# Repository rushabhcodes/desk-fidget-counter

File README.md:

# Desk fidget counter

A USB-powered scroll ring with a fixed **1.28-inch round display**. It counts complete turns, retains the count in FRAM, and shows your computer’s clock, CPU/RAM usage and battery through a USB companion app.

Short-press the front button to switch between scrolling and counting only. Hold for three seconds to clear the count. The screen and cable stay fixed while the outer grip rotates.

## Board and enclosure

- **Two-layer, 1.6 mm PCB**, with all 52 fitted components on top. USB-C is on the rear; a 14×7 mm curved button with guided travel and foam return operates the front Omron switch.
- **Six product prints and four screws**, in an approximately **Ø89.4 × 19.5 mm** body, with the button inside its circular outline. The optical skirt is integral to the grip; the screen carrier and bezel share two screws.
- **One complete 6712ZZ bearing object** in the CAD viewer, including its races, shields, balls and cage. Calibrate the printed bearing fits with the coupons before printing the enclosure.
- The source defines connectivity, supplier footprints, placement and fabrication rules. F1 uses independently checked external routing through TSCircuit’s documented custom-router interface; the stored copper is guarded against changes to its input. See [routing](routing/README.md).

**Current electronics: RP2040 PCB F1 / firmware 6.0.0.** The STM32 has been replaced with an RP2040, 2 MB Winbond boot flash, a 12 MHz Abracon crystal, local supply bypassing and 27 Ω USB termination. The PCB outline and connector, sensor and switch datums remain compatible with the Ø89.4 mm E14 enclosure and its recessed circular button. Local circuit, fabrication and assembly checks pass for a first prototype. The older E6 archive targets STM32; use the matching [F1 fabrication kit](release/desk-knob-f1-e14-fabrication.zip). See [readiness](validation/readiness.json) and the [firmware/programming guide](firmware/README.md).

[Visual CAD audit](mechanical/AUDIT.md): fourteen inspection views, corrected carrier screw bores and reserved space for screen rear electronics; enclosure height remains 19.5 mm.

[E14 visual review](mechanical/VISUAL-REVIEW.md): a continuous fixed collar covers the open underside of the screen bezel. It belongs to the existing carrier and retains the 0.8 mm rotating seam, body dimensions, six prints and four screws.

Widget v6.0.4 includes the upstream copper-pour visibility fix. Both the C1 pad connection and its long GND continuation are visible. [Trace visibility checks](validation/TRACE-VISIBILITY.md)

## What to buy outside JLCPCB

Quantities below are for **one complete device**. A complete JLCPCB **assembly** order supplies the PCB and its 52 fitted electronic components, including the MCU, optical sensor, FRAM, USB connector, front button, J4 programming header and J6 removable display header. A bare-PCB order supplies the board only.

| Qty | Buy or supply separately | Specification and purpose |
|---|---|---|
| 1 kit | [Waveshare 19192 display](https://www.waveshare.com/product/1.28inch-lcd-module.htm) | Non-touch, 1.28-inch, 240×240 GC9A01 module. The supplied PH-to-jumper lead is unused. Connect using replacement H1 below. |
| 1 | [Complete 6712ZZ bearing](https://maysmeprecision.com/Show/?Cid=677) | **60 mm bore × 75 mm OD × 7 mm**, double metal shields. Buy the assembled bearing; its internal balls/races are not separate purchases. |
| 6 | [E14 printed enclosure parts](mechanical/stl) | `base`, `lid`, `knob`, `screen-carrier`, `screen-bezel`, `button-cap`. PLA; the grip’s integral optical track must be **opaque at 950 nm**. Black colour alone does not establish this. Print the fit coupons first. |
| 2 | Countersunk **DIN 965 M2×6** screws | Attach the base and lid. Nominal head Ø3.8 mm; check the actual purchased head/drive against the model. |
| 2 | Countersunk **DIN 965 M2×10** screws | One shared pair retains the screen bezel and carrier on the braced screw supports. |
| 1 small piece | [PORON 4701-30-20062-04 foam](https://www.rogerscorp.com/elastomeric-material-solutions/poron-industrial-polyurethanes/poron-4701-30) | **1.57 mm** nominal, 320 kg/m³. Cut four Ø4 mm and two Ø2.6 mm PCB capture pads, plus four 2×1.6 mm pieces for two stacked button-return pads; a 20×20 mm sample is sufficient. |
| 1 small piece | [3M 467MP transfer adhesive](https://www.3m.com/3M/en_US/p/dc/v000185218/) | **0.05 mm** adhesive for the six PCB pads and the two stacked button-return pads. The integral optical skirt needs no separate adhesive joint. |
| As needed | [3M 5413 polyimide tape](https://www.3m.co.uk/3M/en_GB/p/d/v000091659/) | **0.069 mm** insulation over inspected underside solder wells. Trim through-hole tails/joints to the documented ≤0.8 mm allowance first. |
| 1 assembled lead | **H1 keyed display harness** | Order a crimped **JST SHR-08V-S-B to PHR-8**, eight wires, straight circuit mapping 1→1 through 8→8, **44±1 mm free insulation between rear housing exits**. [Parts and drawing](manufacturing/WIRING.md). This custom lead is separate from both the display kit and JLCPCB assembly. |
| 1, reuse if suitable | USB data cable | USB-C at the device; ordinary USB 2.0 data is sufficient. Check the plug against the enclosure’s documented 13.4×6.9 mm approach gauge. |
| Optional: 3 | Adhesive silicone feet | Approximately Ø5×1 mm. These add 1 mm to the nominal body height. |

**H1 is a replacement crimped cable, purchased separately. J6’s keyed JST-SH socket is fitted by JLCPCB, including in the SMT-only option.** The display, bearing, printed parts and final wiring/mechanical assembly are not supplied as part of PCB assembly.

### Programming equipment and tools

These items are reusable and removed before closing the enclosure:

| Qty | Item | Requirement |
|---|---|---|
| 1 | SWD programmer | CMSIS-DAP / Raspberry Pi Debug Probe supporting RP2040. USB powers the board; VTref is a sense connection. |
| 1 | J4 programming lead | JST **PHR-6**, 2.0 mm PH series, with the correct probe-end termination. A precrimped lead can be used. If making it, use six **SPH-004T-P0.5S** contacts plus spares and qualified 32–28 AWG wire, insulation Ø0.5–0.9 mm. See the [physical pin map](https://github.com/rushabhcodes/desk-fidget-counter/blob/main/manufacturing/WIRING.md). |
| 1, only for SMT-only PCBA | J4 board header | The **51-placement SMT-only** option includes J6 and leaves only **JST B6B-PH-K-S(LF)(SN), C131342** for local through-hole soldering. Complete assembly has 52 placements. |

Have solder/flux and a soldering setup, wire stripper, flush cutters, multimeter, caliper, an M2×0.4 tap and a screwdriver matching your screws. Follow the [printing and fit guide](mechanical/FIT.md); the supplied print orientations and support notes matter.

## Software and controls

Flash firmware 6.0.0 through J4 SWD or the RP2040 USB UF2 bootloader, then initialize a fresh FRAM with a three-second button hold or the explicit console command in the [firmware guide](https://github.com/rushabhcodes/desk-fidget-counter/blob/main/firmware/README.md).

For laptop information:

```sh
python -m pip install -r companion/requirements.txt
python companion/dashboard.py
```

The [companion guide](https://github.com/rushabhcodes/desk-fidget-counter/blob/main/companion/README.md) covers macOS, Windows and Linux. Counting and scrolling work without the companion while USB is awake. USB suspend switches the display and encoder off; turns during suspend are not measured.

## Build and validation

```sh
bun install --frozen-lockfile
bun run typecheck && bun run test:route-display && bun run test
bun run check:netlist && bun run check:schematic
bun run build
bun run check:placement && bun validation/check-design.mjs
bun run check:footprints && bun run check:shorts && bun run check:assembly
```

The lockfile pins tscircuit `0.0.3157`, core `0.0.2340` and the CLI’s KiCad export dependency. Regenerate the PCB, schematic and 3D snapshots with `bun run tsci snapshot '*.circuit.tsx' --update --3d`.

`assembly.circuit.tsx` is the complete product; `index.circuit.tsx` is the bare PCB. The build stages the checked full assembly at `dist/circuit.json` for publication. Source, package CAD, prints and wiring are included in the repository. The [F1/E14 fabrication kit](release/desk-knob-f1-e14-fabrication.zip) includes matching Gerbers, BOM/CPL, physical pin maps, independent checks and RP2040 firmware. Follow the [upload guide](manufacturing/current/README.md). Final factory preview and physical prototype bring-up remain; no supplier upload or order has been made.

- [Assembly steps](https://github.com/rushabhcodes/desk-fidget-counter/blob/main/ASSEMBLY.md) · [Wiring and programming connections](https://github.com/rushabhcodes/desk-fidget-counter/blob/main/manufacturing/WIRING.md)
- [Mechanical source and CAD](https://github.com/rushabhcodes/desk-fidget-counter/blob/main/mechanical/README.md) · [Model provenance and limitations](https://github.com/rushabhcodes/desk-fidget-counter/blob/main/mechanical/vendor/README.md)
- [Manufacturing requirements](https://github.com/rushabhcodes/desk-fidget-counter/blob/main/manufacturing/README.md) · [Validation results](https://github.com/rushabhcodes/desk-fidget-counter/blob/main/validation/REPORT.md) · [First-prototype bring-up](https://github.com/rushabhcodes/desk-fidget-counter/blob/main/validation/BRINGUP.md)

Inspired by the [Ploopy Knob](https://ploopy.co/knob/) and [original fidget counter](https://tscircuit.com/rushabhcodes/fidget-counter). Project code and original geometry are MIT; purchased-part assets retain their upstream rights.

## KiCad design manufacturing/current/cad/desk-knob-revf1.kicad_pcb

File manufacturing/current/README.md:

# Desk knob — RP2040 PCB F1 / enclosure E14

Checked 10 November 2026 against the current source. Local circuit, independent fabrication and assembly checks pass for **first-prototype manufacture**. This kit contains RP2040 hardware and firmware 6.0.0, with the recessed curved button inside the Ø89.4×19.5 mm E14 enclosure. Final manufacturer DFM/feeder preview and physical bring-up remain. No supplier upload, purchase or stock allocation was performed.

## Upload files

1. Upload **Gerbers-F1.zip** for PCB fabrication. The outer review ZIP also contains CAD, evidence, firmware and prints; it is not the Gerber upload.
2. For **52-part complete assembly**, upload **BOM-complete.csv + CPL-complete.csv** and confirm a service including the J4 through-hole header.
3. For **51-part SMT assembly**, upload **BOM-smt.csv + CPL-smt.csv**. Fit only J4, JST B6B-PH-K-S(LF)(SN) / C131342, locally. J6 is already fitted.
4. Check every exact MPN, feeder origin, asymmetric rotation and pin 1 against **physical-pin-map.csv** and **assembly/assembly-top.svg** before payment. CPL and Gerbers share their origin, including negative Y; do not mirror, take absolute coordinates or edit rotations independently.

## Board settings

| Item | Specification |
|---|---|
| Material | FR-4, Tg ≥135°C |
| Layers / copper / thickness | 2 layers / 1 oz / 1.6 mm nominal |
| Finish / mask / silk | ENIG / green / white |
| Unit outline | 68×83.5 mm clipped round profile with USB/button tabs |
| Internal window | 34.6×40.6 mm, R2 corners; preserve the Gerber contour |
| Vias | 50 at Ø0.20 drill / Ø0.50 pad; 48 at Ø0.30 / Ø0.60 mm |
| Copper rules | ≥0.10 mm track/gap, ≥0.15 mm component-pad gap, ≥0.30 mm edge clearance |
| USB shield slots | Four plated 0.60×1.50/1.60 mm slots |
| Assembly | 52 top placements / 27 exact MPN BOM lines |

E14 adds a continuous fixed collar to the existing screen carrier. Keep the 0.8 mm rotating seam open; see enclosure/VISUAL-REVIEW.md for the complete visual review. The body remains Ø89.4×19.5 mm with six prints and four screws.

The 98 vias retain ≥0.15 mm annular rings and their drills do not intersect SMT paste. No via-in-pad process is required. Confirm tooling/support for the irregular outline and large internal window; removable panel rails must stay outside the finished outline. USB full-speed signal integrity has not been measured.

## Product assembly and programming

J4 is the only through-hole header. Trim its underside tails/joints to ≤0.8 mm, inspect/deburr and insulate the specified solder wells before enclosure assembly. The Waveshare display, complete 6712ZZ bearing, six printed parts, screws, foam and custom H1 harness are separate from PCBA. H1 is a keyed crimped SH8-to-PH8 lead, 44±1 mm free insulation, straight circuits 1→1 through 8→8; see **WIRING.md** and **LCD-harness.csv**. The display kit's jumper lead is unused.

**enclosure/stl/** contains the six E14 product prints and three fit coupons. Follow the print poses and fit notes, and use **ASSEMBLY.md** for the sequence. Actual printed fits, optical opacity and button force/life require validation.

Use **firmware/desk-knob.uf2** with the RP2040 ROM USB bootloader or **firmware/desk-knob.elf** through J4 SWD. See **firmware/README.md** for the exact procedure. Initialize a fresh FRAM deliberately with a three-second button hold, then perform **BRINGUP.md** checks. Historical STM32 programming procedures and images do not apply.

## Evidence and file integrity

**checks/** includes zero-violation/zero-open KiCad DRC, native-copper/pad/drill preservation, Gerber/Excellon parsing, BOM/CPL and physical pin maps, annuli/paste clearances, local signal paths, firmware image and assembly audit evidence. All 27 exact part identities were publicly purchasable on 10 November 2026; stock is unreserved. Final allocation, purchasing/attrition quantities and feeder/rotation approval require the factory quote/preview. MCU unit pricing does not establish a lower complete PCBA price.

**cad/** contains the finalized source-derived KiCad board/project/rules and exact generated footprints. **manifest.json** binds the kit to the checked source. **SHA256SUMS.txt** covers every kit file except itself. Keep this F1 hardware, BOM/CPL and firmware together.

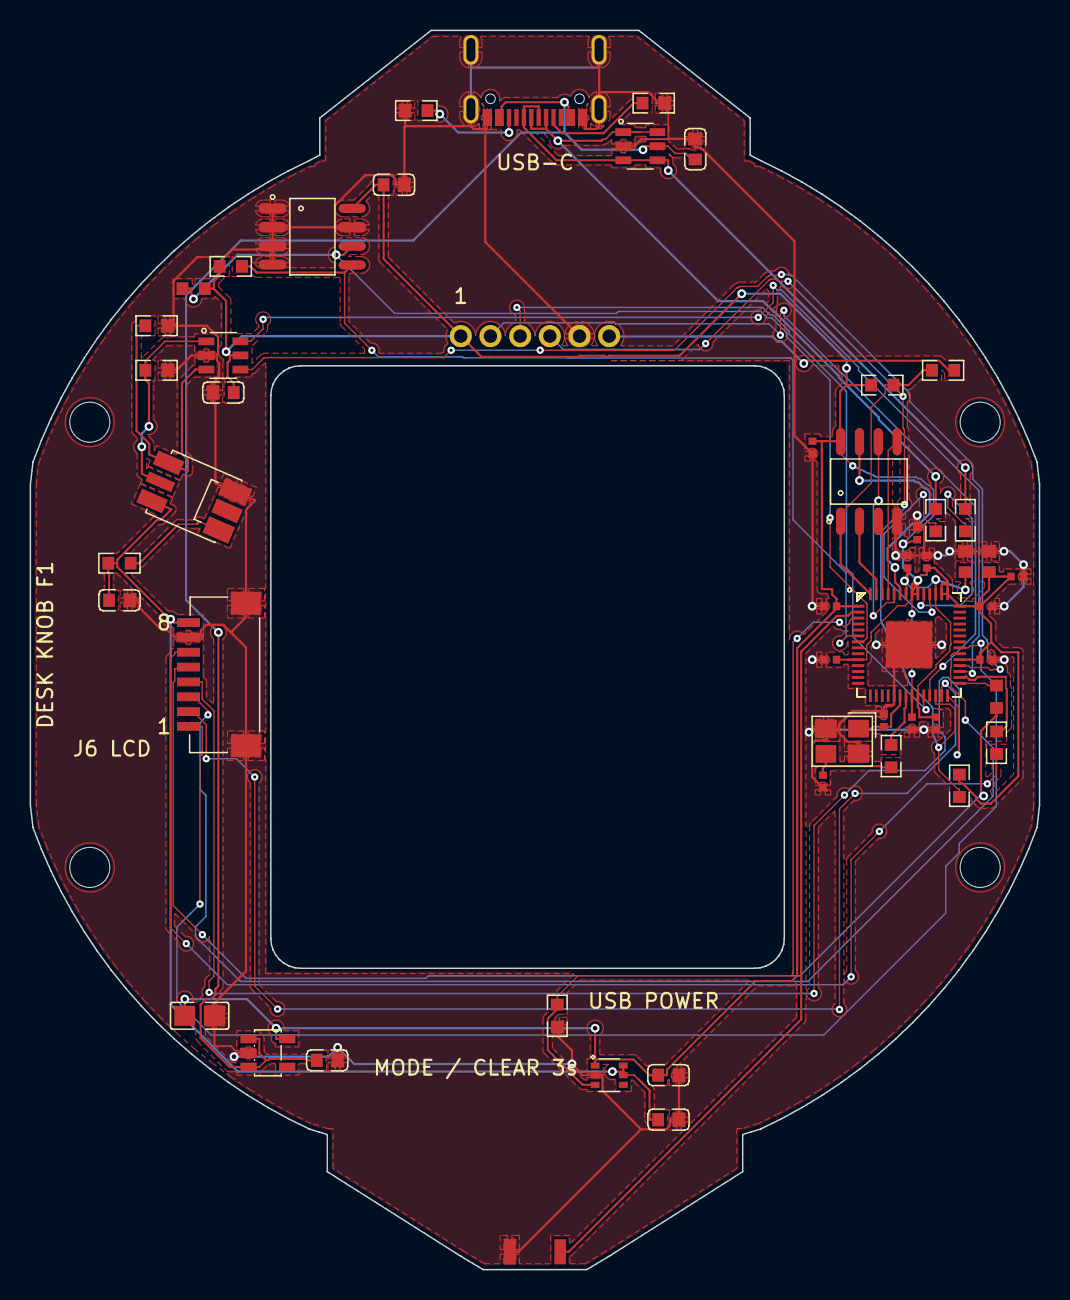
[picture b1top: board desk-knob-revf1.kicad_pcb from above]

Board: 2 copper layers, 68.0 x 83.5 mm, 52 parts (0 on the bottom side), 41 nets.

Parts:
C1: 100nF; GRM188R71C104KA01D__C1
C2: 1uF; GRM188R61A105KA61D__C2
C3: 1uF; GRM188R61A105KA61D__C3
C5: 1uF; GRM188R61A105KA61D__C5
C6: 4.7uF; CL21A475KOFNNNE__C6
C7: 100nF; GRM155R71C104KA88D__C7
C8: 100nF; GRM155R71C104KA88D__C8
C9: 100nF; GRM155R71C104KA88D__C9
C10: 100nF; GRM155R71C104KA88D__C10
C11: 100nF; GRM155R71C104KA88D__C11
C12: 100nF; GRM155R71C104KA88D__C12
C13: 100nF; GRM155R71C104KA88D__C13
C14: 100nF; GRM188R71C104KA01D__C14
C15: 1uF; GRM188R61A105KA61D__C15
C16: 100nF; GRM188R71C104KA01D__C16
C17: 100nF; GRM155R71C104KA88D__C17
C18: 100nF; GRM155R71C104KA88D__C18
C19: 100nF; GRM155R71C104KA88D__C19
C20: 1uF; GRM188R61A105KA61D__C20
C21: 1uF; GRM188R61A105KA61D__C21
C22: 100nF; GRM155R71C104KA88D__C22
C23: 15pF; 0402CG150J500NT__C23
C24: 15pF; 0402CG150J500NT__C24
J1: J1; TYPEC-309-ACP16L65__J1
J4: J4; B6B-PH-K-S_LF_SN__J4
J6: J6; SM08B-SRSS-TB_LF_SN__J6
R1: 5.1kΩ; RC0603FR-075K1L__R1
R2: 5.1kΩ; RC0603FR-075K1L__R2
R3: 27Ω; 0603WAF270JT5E__R3
R4: 27Ω; 0603WAF270JT5E__R4
R5: 1kΩ; 0603WAF1001T5E__R5
R6: 1kΩ; 0603WAF1001T5E__R6
R7: 10kΩ; RC0603FR-0710KL__R7
R10: 10kΩ; RC0603FR-0710KL__R10
R12: 4.7kΩ; RC0603FR-074K7L__R12
R13: 4.7kΩ; RC0603FR-074K7L__R13
R21: 100kΩ; RC0603FR-07100KL__R21
R24: 150Ω; RC0603FR-07150RL__R24
R25: 22kΩ; RC0603FR-0722KL__R25
R26: 22kΩ; RC0603FR-0722KL__R26
R27: 22Ω; RC0603FR-0722RL__R27
R28: 22Ω; RC0603FR-0722RL__R28
SW1: SW1; B3U-3000P__SW1
U1: RP2040; RP2040__U1
U2: TCUT1600X01; TCUT1600X01__U2
U3: MB85RC256VPNF-G-AMERE2; MB85RC256VPNF-G-AMERE2__U3
U4: TPS22919DCKR; TPS22919DCKR__U4
U5: TLV75533PDBVR; TLV75533PDBVR__U5
U6: USBLC6-2SC6; USBLC6-2SC6__U6
U7: SN74LVC2G17DBVR; SN74LVC2G17DBVR__U7
U8: W25Q16JVSNIQ; W25Q16JVSNIQ__U8
X1: X1; ABM8-272-T3__X1

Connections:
BOOTSEL: J4.6, R6.2
CC1: J1.39, R1.1
CC2: J1.33, R2.1
ENC_A: U1.31, U7.6
ENC_B: U1.32, U7.4
GND: C1.2, C2.2, C3.2, C5.2, C6.2, C7.2, C8.2, C9.2, C10.2, C11.2, C12.2, C13.2, C14.2, C15.2, C16.2, C17.2, C18.2, C19.2, C20.2, C21.2, C22.2, C23.2, C24.2, J1.25, J1.26, J1.27, J1.28, J1.29, J1.30, J1.43, J1.44, J4.5, J6.7, J6.9, J6.10, R1.2, R2.2, R21.2, R25.2, R26.2, SW1.2, U1.19, U1.57, U2.3, U3.1, U3.2, U3.3, U3.4, U3.7, U4.2, U5.2, U6.2, U7.2, U8.4, X1.2, X1.4
IR_A: R24.2, U2.1
LCD_BL: J6.1, U1.35
LCD_CS: J6.4, U1.28
LCD_DC: J6.3, U1.34
LCD_MOSI: J6.6, R28.2
LCD_RST: J6.2, U1.27
LCD_SCK: J6.5, R27.2
MODE_BTN: SW1.1, U1.2
OPT_A: R25.1, U2.5, U7.1
OPT_B: R26.1, U2.4, U7.3
PERIPH_3V3: C3.1, C15.1, J6.8, R24.1, U2.6, U4.5, U4.6
PERIPH_EN: R21.1, U1.3, U4.3
QSPI_SCLK: U1.52, U8.6
QSPI_SD0: U1.53, U8.5
QSPI_SD1: U1.55, U8.2
QSPI_SD2: U1.54, U8.3
QSPI_SD3: U1.51, U8.7
QSPI_SS: R6.1, R7.1, U1.56, U8.1
RUN: J4.4, R10.1, U1.26
SCL: R13.2, U1.7, U3.6
SDA: R12.2, U1.6, U3.5
SPI_MOSI: R28.1, U1.30
SPI_SCK: R27.1, U1.29
SWCLK: J4.3, U1.24
SWDIO: J4.2, U1.25
USB_DM: J1.36, J1.38, R3.2, U6.1, U6.6
USB_DM_MCU: R3.1, U1.46
USB_DP: J1.35, J1.37, R4.2, U6.3, U6.4
USB_DP_MCU: R4.1, U1.47
V1V1: C18.1, C19.1, C21.1, U1.23, U1.45, U1.50
V3V3: C2.1, C6.1, C7.1, C8.1, C9.1, C10.1, C11.1, C12.1, C13.1, C14.1, C16.1, C17.1, C20.1, C22.1, J4.1, R7.2, R10.2, R12.1, R13.1, U1.1, U1.10, U1.22, U1.33, U1.42, U1.43, U1.44, U1.48, U1.49, U3.8, U4.1, U5.5, U7.5, U8.8
VBUS: C1.1, C5.1, J1.31, J1.32, J1.41, J1.42, U5.1, U5.3, U6.5
XIN: C23.1, U1.20, X1.1
XOUT: R5.1, U1.21
XTAL_OUT: C24.1, R5.2, X1.3

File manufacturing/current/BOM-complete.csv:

Comment,Designator,Footprint,LCSC Part #,Manufacturer,MPN
GRM188R71C104KA01D / 100nF 16V X7R 10%,"C1,C14,C16",0603,C45000,Murata Electronics,GRM188R71C104KA01D
GRM188R61A105KA61D / 1uF 10V X5R 10%,"C2,C3,C5,C15,C20,C21",0603,C86012,Murata Electronics,GRM188R61A105KA61D
CL21A475KOFNNNE / 4.7uF 16V X5R 10%,C6,0805,C1746,Samsung Electro-Mechanics,CL21A475KOFNNNE
GRM155R71C104KA88D / 100nF 16V X7R 10%,"C7,C8,C9,C10,C11,C12,C13,C17,C18,C19,C22",0402,C71629,Murata Electronics,GRM155R71C104KA88D
0402CG150J500NT / 15pF 50V C0G 5% crystal load,"C23,C24",0402,C1548,FH (Guangdong Fenghua Advanced Tech),0402CG150J500NT
"TYPEC-309-ACP16L65 / USB-C receptacle, 6.5mm body, 3A/5V per drawing; USB 2.0 D+/D- and CC contacts",J1,"SMD, 16 contacts / 4 shell stakes",C2909598,XUNPU,TYPEC-309-ACP16L65
B6B-PH-K-S(LF)(SN) / 6-pin top-entry programming header,J4,JST-PH-6-P2.0-THT,C131342,JST,B6B-PH-K-S(LF)(SN)
SM08B-SRSS-TB(LF)(SN) / Keyed 8-pin side-entry SMT display socket; two grounded hold-downs,J6,JST-SH-8-P1.0-SMT-side-entry,C160407,JST,SM08B-SRSS-TB(LF)(SN)
RC0603FR-075K1L / 5.1k 1% 100mW,"R1,R2",0603,C105580,YAGEO,RC0603FR-075K1L
0603WAF270JT5E / 27ohm 1% USB series termination,"R3,R4",0603,C25190,UNI-ROYAL(Uniroyal Elec),0603WAF270JT5E
0603WAF1001T5E / 1kohm 1% clock damping / BOOTSEL isolation,"R5,R6",0603,C21190,UNI-ROYAL(Uniroyal Elec),0603WAF1001T5E
RC0603FR-0710KL / 10k 1% 100mW,"R7,R10",0603,C98220,YAGEO,RC0603FR-0710KL
RC0603FR-074K7L / 4.7k 1% 100mW,"R12,R13",0603,C99782,YAGEO,RC0603FR-074K7L
RC0603FR-07100KL / 100k 1% 100mW,R21,0603,C14675,YAGEO,RC0603FR-07100KL
RC0603FR-07150RL / 150R 1% 100mW,R24,0603,C114608,YAGEO,RC0603FR-07150RL
RC0603FR-0722KL / 22k 1% 100mW,"R25,R26",0603,C114065,YAGEO,RC0603FR-0722KL
RC0603FR-0722RL / 22R 1% 100mW,"R27,R28",0603,C107701,YAGEO,RC0603FR-0722RL
B3U-3000P / side-actuated SMT switch,SW1,Omron-B3U-3000P,C963349,Omron Electronics,B3U-3000P
RP2040 / Dual Cortex-M0+ MCU; external boot flash,U1,QFN-56-EP7x7-P0.4,C2040,Raspberry Pi,RP2040
TCUT1600X01 / dual optical interrupter 3mm slot,U2,Vishay-TCUT1600-SMD-6,C511085,Vishay Intertech,TCUT1600X01
MB85RC256VPNF-G-AMERE2 / 256kbit I2C FRAM,U3,SOP-8-150mil,C45273903,RAMXEED/FUJITSU,MB85RC256VPNF-G-AMERE2
TPS22919DCKR / load switch,U4,SC70-6,C2149796,Texas Instruments,TPS22919DCKR
TLV75533PDBVR / 3.3V LDO,U5,SOT-23-5,C404027,Texas Instruments,TLV75533PDBVR
USBLC6-2SC6 / ST USB ESD array,U6,SOT-23-6,C7519,STMicroelectronics,USBLC6-2SC6
SN74LVC2G17DBVR / TI dual Schmitt buffer,U7,SOT-23-6,C10429,Texas Instruments,SN74LVC2G17DBVR
W25Q16JVSNIQ / Winbond 16Mbit/2MB 3.3V QSPI NOR flash,U8,SOIC-8-150mil,C2456211,Winbond Elec,W25Q16JVSNIQ
"ABM8-272-T3 / Abracon 12MHz, CL10pF, 50ohm ESR crystal",X1,SMD-3225-4P,C20625731,Abracon LLC,ABM8-272-T3

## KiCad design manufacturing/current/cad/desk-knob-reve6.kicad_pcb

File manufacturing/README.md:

# Manufacturing source / PCB RP2040 F1, mechanics E14

**RP2040 F1 passes local first-prototype fabrication and assembly checks.** Use [the F1/E14 kit](../release/desk-knob-f1-e14-fabrication.zip) or the matching files in [manufacturing/current](current/README.md). The population is 52 parts (51 SMT plus the J4 through-hole header), with firmware 6.0.0. Final factory DFM, part/feeder/rotation approval and physical bring-up remain. The historical E6/E13 archive targets STM32 and must not be mixed with F1.

The obsolete v5.4.0 Gerbers, KiCad board, BOM/CPL, order kit and manifest were removed from this working revision because they contain the undersized U3 FRAM footprint and outdated assembly angles. They remain in Git history and the held old release; do not order them or mix them with new exports. Current part identities and exact supplier footprints live in [the catalogue](../reference/jlcpcb-parts.json), [import provenance](../reference/jlcpcb-footprints.json) and `imports/jlc`.

## Board specification

| Parameter | Requirement |
|---|---|
| Outline | Clipped Ø72 mm body with integral USB/button tabs; 68×83.5 mm total; 34.6×40.6 mm R2 window; four Ø2.7 mm NPTH at (±30, ±15) mm |
| Material | FR-4, 1.6 mm nominal, Tg ≥135°C |
| Copper | Two layers, 1 oz outer copper |
| Finish | ENIG; green solder mask, white silkscreen |
| Track | ≥0.10 mm fabrication limit; routing requests 0.15 mm; measured widths in the validation report |
| Clearance | ≥0.10 mm track/via copper; ≥0.15 mm component pad-to-pad; ground pour clearance 0.25 mm |
| Routing via | Ø0.30 mm drill / Ø0.60 mm pad preferred; Ø0.20 mm / Ø0.50 mm for dense fanout; both retain ≥0.15 mm annular ring |
| Drill spacing | Via drill-edge ≥0.20 mm; component PTH drill-edge ≥0.45 mm |
| Hole-to-copper | NPTH ≥0.20 mm; via drill ≥0.20 mm; component plated drill ≥0.28 mm |
| Copper to edge | ≥0.30 mm; ground pours inset 0.40 mm |
| Assembly | 52 fitted components, all top; J4 JST PH6 and J6 keyed JST-SH8 SMT socket fitted |
| Local assembly | Fit crimped replacement H1; continuity/isolation check; trim only J4 tails to ≤0.8mm |

[Fabrication rules](../reference/fabrication-rules.json) record the checked [JLCPCB capabilities](https://jlcpcb.com/capabilities/pcb-capabilities/). Keep 1 oz copper. This is not a controlled-impedance design; USB full-speed signal integrity is a prototype test.

J1 remains at (0,+37.55)mm and SW1 at (0,-40.9)mm, operated by the captive printed cap. J6 is JST SM08B-SRSS-TB(LF)(SN)/C160407 at (-21.3,-2)mm,90deg,facing +X. Circuits1–8 are BL/RST/DC/CS/CLK/DIN/GND/VCC; anchors9/10 are GND. Connect the display with the separately purchased crimped H1 harness. [Physical circuit map](WIRING.md).

## Verification without producing a kit

```sh
bun install --frozen-lockfile
bun run typecheck && bun run test
bun run check:netlist && bun run check:schematic
bun run build
bun run check:placement
bun validation/check-design.mjs
bun run check:footprints && bun run check:shorts && bun run check:assembly
```

For the independent check, install KiCad 10 CLI and its matching Python `pcbnew` module:

```sh
bunx tsci export dist/index/circuit.json -f kicad_pcb -o /tmp/desk-knob-raw.kicad_pcb
/usr/bin/python3 scripts/export-fabrication.py /tmp/desk-knob-raw.kicad_pcb --check-only
```

`--check-only` writes temporary evidence under `/tmp`; it does not produce an order kit. It checks all 222 pad centres and plated drills against source, applies the documented rules, refills ground zones and removes electrically isolated ground fragments. It requires zero DRC violations/unconnected items, no exclusions and an exact match of every native trace and via before/after. It does not route or repair copper. See [validation results](../validation/REPORT.md).

## Standard USB-C connector

J1 is **XUNPU TYPEC-309-ACP16L65 / C2909598**, selected through TSCI's JLCPCB catalogue. Its exact imported footprint has four **0.60×1.50/1.60 mm** plated slots, meeting the published ≥2:1 length/width guidance, and two Ø0.65 mm locating holes with approximately 0.364 mm to adjacent pads. Its drawing agrees with the pad/hole pattern. The housing is 6.5 mm long and 3.16 mm high; the unscaled supplier CAD is aligned to the real SMT seating plane. The socket mouth reaches Y42.1865 mm, within the rear opening; a 13.4×6.9 mm plug approach gauge clears the PCB, packages, shell and grip. The circular product stays 19.5 mm high.

The original C165948 connector and its short slots are removed from the fitted design. No supplier pad or drill geometry was resized. [Selection and drawing evidence](../reference/usb-connector-selection.json) and [measured slot checks](../validation/supplier-review.json).

## When you export later

Use the bare PCB entrypoint [index.circuit.tsx](../index.circuit.tsx) for factory exports. Export all Gerbers, plated/nonplated drills, BOM and placement files from that same freshly built revision. Verify window/outline geometry, exact MPNs, 52 top placements including fitted J4 and J6. Do not reuse the held old CSVs. JLCPCB feeder origins and zero angles still need confirmation against the physical copper and datasheet pin 1 in your final upload preview; a generic 3D model is insufficient.

[JLCPCB guidance](jlcpcb/README.md) records part matching/cost evidence and the remaining supplier steps. The screen, bearing, six prints and final wire/mechanical assembly are separate from PCB assembly. The first prototype still needs [bring-up](../validation/BRINGUP.md) and [fit verification](../mechanical/FIT.md).

The independent KiCad check uses 1 nm coordinate resolution. A duplicate zero-length exporter segment may be omitted only when its entire copper disk is already covered by an equal or wider same-net endpoint. The check records each omission and rejects uncovered segments. Native circuit JSON, routed copper geometry, vias and connections remain unchanged.

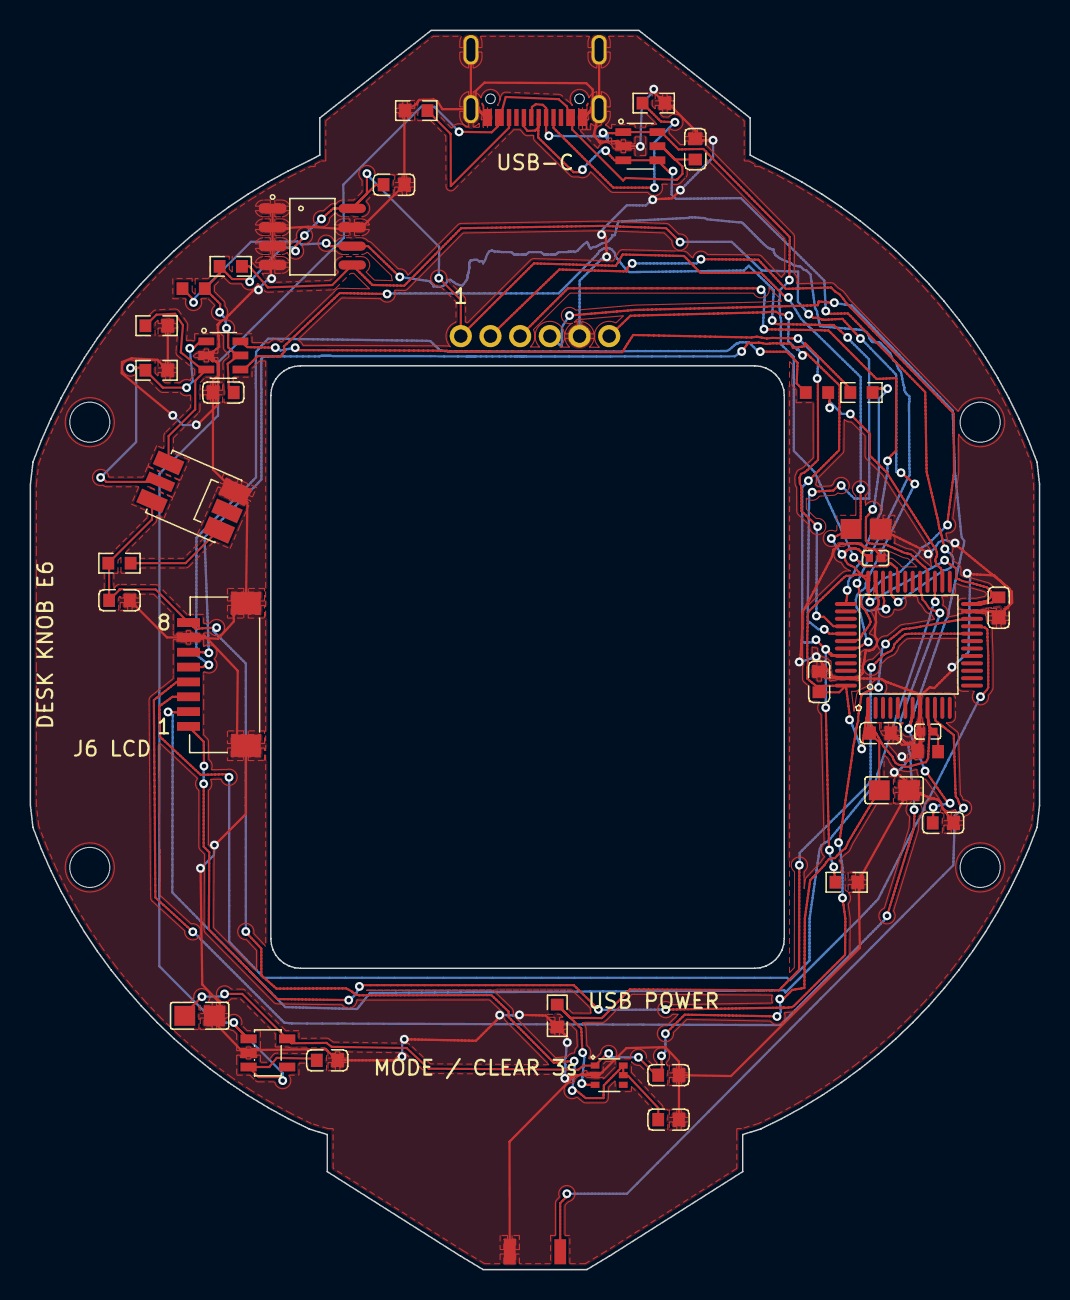
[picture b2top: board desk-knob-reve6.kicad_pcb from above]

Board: 2 copper layers, 68.0 x 83.5 mm, 39 parts (0 on the bottom side), 29 nets.

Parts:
C1: 100nF; GRM188R71C104KA01D__C1
C2: 1uF; GRM188R61A105KA61D__C2
C3: 1uF; GRM188R61A105KA61D__C3
C5: 1uF; GRM188R61A105KA61D__C5
C6: 4.7uF; CL21A475KOFNNNE__C6
C7: 100nF; GRM188R71C104KA01D__C7
C8: 10nF; GRM155R71H103KA88D__C8
C9: 100nF; GRM188R71C104KA01D__C9
C10: 100nF; GRM155R71C104KA88D__C10
C11: 100nF; GRM188R71C104KA01D__C11
C12: 4.7uF; CL21A475KOFNNNE__C12
C13: 100nF; GRM188R71C104KA01D__C13
C14: 100nF; GRM188R71C104KA01D__C14
C15: 1uF; GRM188R61A105KA61D__C15
C16: 100nF; GRM188R71C104KA01D__C16
C17: 1uF; GRM188R61A105KA61D__C17
C18: 4.7uF; CL21A475KOFNNNE__C18
J1: J1; TYPEC-309-ACP16L65__J1
J4: J4; B6B-PH-K-S_LF_SN__J4
J6: J6; SM08B-SRSS-TB_LF_SN__J6
R1: 5.1kΩ; RC0603FR-075K1L__R1
R2: 5.1kΩ; RC0603FR-075K1L__R2
R10: 10kΩ; RC0603FR-0710KL__R10
R12: 4.7kΩ; RC0603FR-074K7L__R12
R13: 4.7kΩ; RC0603FR-074K7L__R13
R21: 100kΩ; RC0603FR-07100KL__R21
R24: 150Ω; RC0603FR-07150RL__R24
R25: 22kΩ; RC0603FR-0722KL__R25
R26: 22kΩ; RC0603FR-0722KL__R26
R27: 22Ω; RC0603FR-0722RL__R27
R28: 22Ω; RC0603FR-0722RL__R28
SW1: SW1; B3U-3000P__SW1
U1: STM32F072CBT6; STM32F072CBT6__U1
U2: TCUT1600X01; TCUT1600X01__U2
U3: MB85RC256VPNF-G-AMERE2; MB85RC256VPNF-G-AMERE2__U3
U4: TPS22919DCKR; TPS22919DCKR__U4
U5: TLV75533PDBVR; TLV75533PDBVR__U5
U6: USBLC6-2SC6; USBLC6-2SC6__U6
U7: SN74LVC2G17DBVR; SN74LVC2G17DBVR__U7

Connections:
BOOT0: J4.6, R10.1, U1.44
CC1: J1.39, R1.1
CC2: J1.33, R2.1
ENC_A: U1.40, U7.6
ENC_B: U1.41, U7.4
GND: C1.2, C2.2, C3.2, C5.2, C6.2, C7.2, C8.2, C9.2, C10.2, C11.2, C12.2, C13.2, C14.2, C15.2, C16.2, C17.2, C18.2, J1.25, J1.26, J1.27, J1.28, J1.29, J1.30, J1.43, J1.44, J4.5, J6.7, J6.9, J6.10, R1.2, R2.2, R10.2, R21.2, R25.2, R26.2, SW1.2, U1.8, U1.23, U1.35, U1.47, U2.3, U3.1, U3.2, U3.3, U3.4, U3.7, U4.2, U5.2, U6.2, U7.2
IR_A: R24.2, U2.1
LCD_BL: J6.1, U1.22
LCD_CS: J6.4, U1.29
LCD_DC: J6.3, U1.27
LCD_MOSI: J6.6, R28.2
LCD_RST: J6.2, U1.21
LCD_SCK: J6.5, R27.2
MODE_BTN: SW1.1, U1.10
NRST: C13.1, J4.4, U1.7
OPT_A: R25.1, U2.5, U7.1
OPT_B: R26.1, U2.4, U7.3
PERIPH_3V3: C3.1, C15.1, J6.8, R24.1, U2.6, U4.5, U4.6
PERIPH_EN: R21.1, U1.20, U4.3
SCL: R13.2, U1.42, U3.6
SDA: R12.2, U1.43, U3.5
SPI_MOSI: R28.1, U1.28
SPI_SCK: R27.1, U1.26
SWCLK: J4.3, U1.37
SWDIO: J4.2, U1.34
USB_DM: J1.36, J1.38, U1.32, U6.1, U6.6
USB_DP: J1.35, J1.37, U1.33, U6.3, U6.4
V3V3: C2.1, C6.1, C7.1, C8.1, C9.1, C10.1, C11.1, C12.1, C14.1, C16.1, C17.1, C18.1, J4.1, R12.1, R13.1, U1.1, U1.9, U1.24, U1.36, U1.48, U3.8, U4.1, U5.5, U7.5
VBUS: C1.1, C5.1, J1.31, J1.32, J1.41, J1.42, U5.1, U5.3, U6.5

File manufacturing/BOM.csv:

Reference,Quantity,Value,Manufacturer,MPN,Side,Populate,Assembly notes
C1,1,100nF,Murata,GRM188R71C104KA01D,top,YES,Top reflow
C2,1,1uF,Murata,GRM188R61A105KA61D,top,YES,Top reflow
C3,1,1uF,Murata,GRM188R61A105KA61D,top,YES,Top reflow
C5,1,1uF,Murata,GRM188R61A105KA61D,top,YES,Top reflow
C6,1,4.7uF,Samsung Electro-Mechanics,CL21A475KOFNNNE,top,YES,Top reflow
C7,1,100nF,Murata,GRM188R71C104KA01D,top,YES,Top reflow
C8,1,10nF,Murata,GRM155R71H103KA88D,top,YES,Top reflow
C9,1,100nF,Murata,GRM188R71C104KA01D,top,YES,Top reflow
C10,1,100nF,Murata,GRM155R71C104KA88D,top,YES,Top reflow
C11,1,100nF,Murata,GRM188R71C104KA01D,top,YES,Top reflow
C12,1,4.7uF,Samsung Electro-Mechanics,CL21A475KOFNNNE,top,YES,Top reflow
C13,1,100nF,Murata,GRM188R71C104KA01D,top,YES,Top reflow
C14,1,100nF,Murata,GRM188R71C104KA01D,top,YES,Top reflow
C15,1,1uF,Murata,GRM188R61A105KA61D,top,YES,Top reflow
C16,1,100nF,Murata,GRM188R71C104KA01D,top,YES,Top reflow
C17,1,1uF,Murata,GRM188R61A105KA61D,top,YES,Top reflow
C18,1,4.7uF,Samsung Electro-Mechanics,CL21A475KOFNNNE,top,YES,Top reflow
J1,1,TYPE-C-31-M-12,HRO,TYPE-C-31-M-12,top,YES,Top reflow
J4,1,B6B-PH-K-S(LF)(SN),JST,B6B-PH-K-S(LF)(SN),top,YES,Hand solder
J6,1,61300811021,Würth Elektronik,61300811021,top,NO,DNP optional header; solder shortened included display lead into these pads
R1,1,5.1kΩ,Yageo,RC0603FR-075K1L,top,YES,Top reflow
R2,1,5.1kΩ,Yageo,RC0603FR-075K1L,top,YES,Top reflow
R10,1,10kΩ,Yageo,RC0603FR-0710KL,top,YES,Top reflow
R12,1,4.7kΩ,Yageo,RC0603FR-074K7L,top,YES,Top reflow
R13,1,4.7kΩ,Yageo,RC0603FR-074K7L,top,YES,Top reflow
R21,1,100kΩ,Yageo,RC0603FR-07100KL,top,YES,Top reflow
R24,1,150Ω,Yageo,RC0603FR-07150RL,top,YES,Top reflow
R25,1,22kΩ,Yageo,RC0603FR-0722KL,top,YES,Top reflow
R26,1,22kΩ,Yageo,RC0603FR-0722KL,top,YES,Top reflow
R27,1,22Ω,Yageo,RC0603FR-0722RL,top,YES,Top reflow
R28,1,22Ω,Yageo,RC0603FR-0722RL,top,YES,Top reflow
SW1,1,B3U-3000P,Omron,B3U-3000P,top,YES,Top reflow
U1,1,STM32F072CBT6,STMicroelectronics,STM32F072CBT6,top,YES,Top reflow
U2,1,TCUT1600X01_A,Vishay,TCUT1600X01_A,top,YES,Top reflow
U3,1,MB85RC256VPNF-G-AMERE2,RAMXEED,MB85RC256VPNF-G-AMERE2,top,YES,Top reflow
U4,1,TPS22919DCKR,Texas Instruments,TPS22919DCKR,top,YES,Top reflow
U5,1,TLV75533PDBVR,Texas Instruments,TLV75533PDBVR,top,YES,Top reflow
U6,1,USBLC6-2SC6,STMicroelectronics,USBLC6-2SC6,top,YES,Top reflow
U7,1,SN74LVC2G17DBVR,Texas Instruments,SN74LVC2G17DBVR,top,YES,Top reflow

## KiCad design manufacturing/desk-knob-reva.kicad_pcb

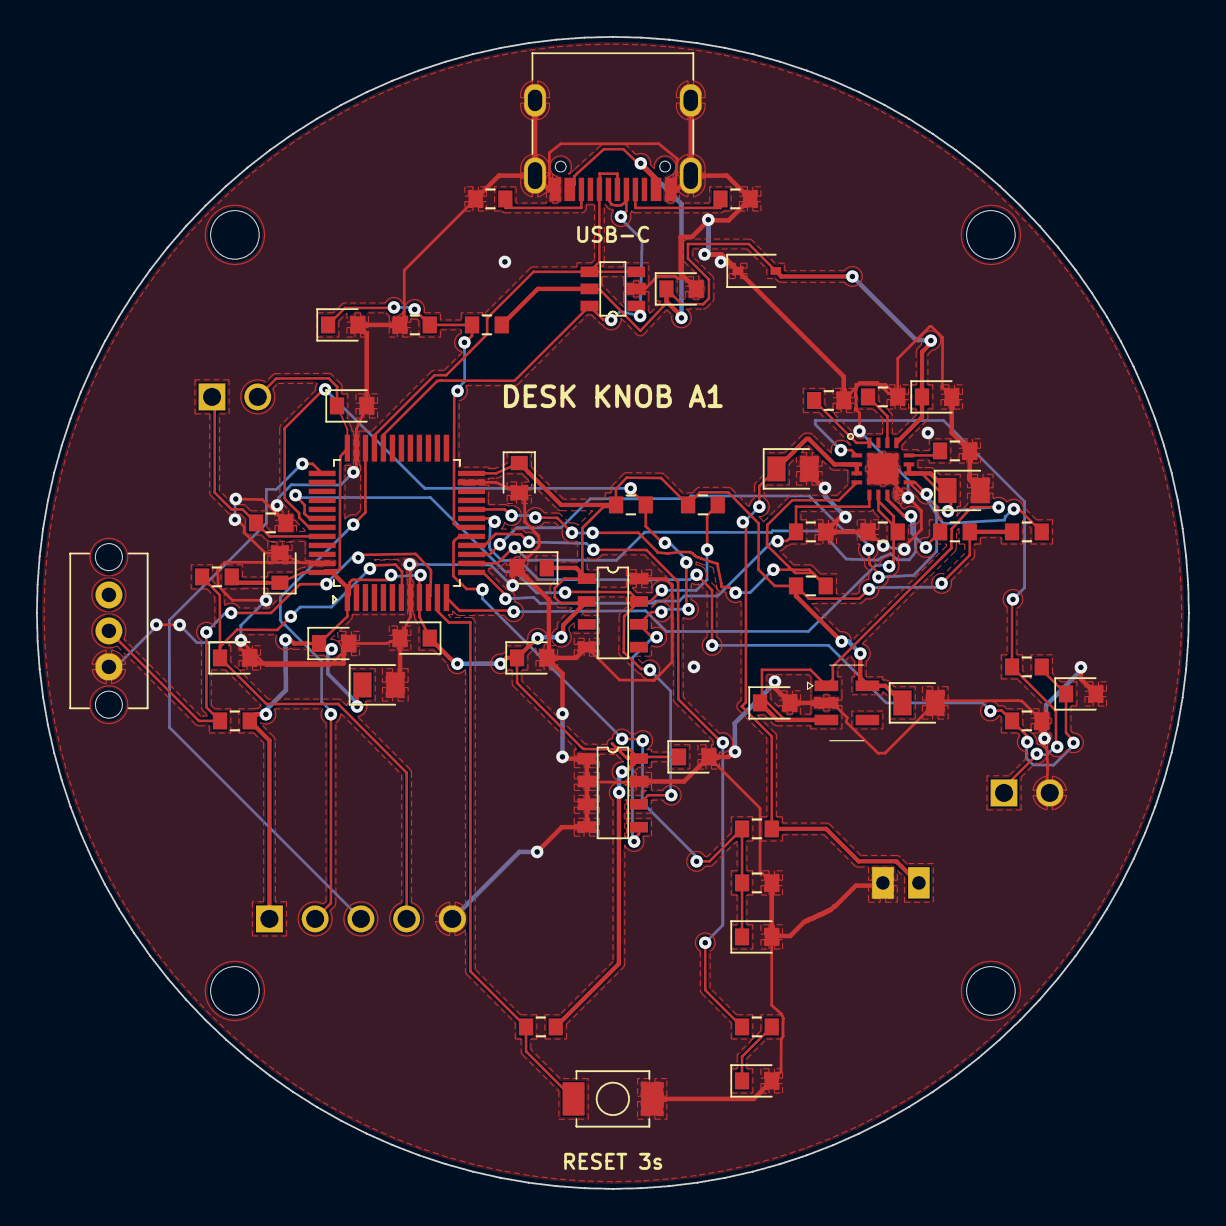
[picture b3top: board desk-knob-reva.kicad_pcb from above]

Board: 2 copper layers, 64.0 x 64.0 mm, 57 parts (1 on the bottom side), 31 nets.

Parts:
C1: 100nF; GRM188R71C104KA01D__C1
C2: 2.2uF; GRM188R61C225KE11D__C2
C3: 10uF; GRM21BR61C106KE15L__C3
C4: 10uF; GRM21BR61C106KE15L__C4
C5: 1uF; GRM188R61A105KA61D__C5
C6: 4.7uF; GRM21BR61A475KA73L__C6
C7: 100nF; GRM188R71C104KA01D__C7
C8: 100nF; GRM188R71C104KA01D__C8
C9: 100nF; GRM188R71C104KA01D__C9
C10: 100nF; GRM188R71C104KA01D__C10
C11: 100nF; GRM188R71C104KA01D__C11
C12: 4.7uF; GRM21BR61A475KA73L__C12
C13: 100nF; GRM188R71C104KA01D__C13
C14: 100nF; GRM188R71C104KA01D__C14
C15: 1uF; GRM188R61A105KA61D__C15
C16: 100nF; GRM188R71C104KA01D__C16
C17: 100nF; GRM188R71C104KA01D__C17
C18: 100nF; GRM188R71C104KA01D__C18
C19: 10nF; GRM188R71H103KA01D__C19
D1: D; PESD5V0S1BA_115__D1
J1: J1; TYPE-C-31-M-12__J1
J2: J2; B2B-PH-K-S_LF_SN__J2
J3: J3; 61300211121__J3
J4: J4; 61300511121__J4
J5: J5; 61300211121__J5
LED1: LTST-C190KGKT; LTST-C190KGKT__LED1
R1: 5.1kΩ; RC0603FR-075K1L__R1
R2: 5.1kΩ; RC0603FR-075K1L__R2
R3: 4.42kΩ; RC0603FR-074K42L__R3
R4: 3.09kΩ; RC0603FR-073K09L__R4
R5: 30kΩ; RC0603FR-0730KL__R5
R6: 100kΩ; RC0603FR-07100KL__R6
R7: 100kΩ; RC0603FR-07100KL__R7
R8: 10kΩ; RC0603FR-0710KL__R8
R9: 10kΩ; RC0603FR-0710KL__R9
R10: 10kΩ; RC0603FR-0710KL__R10
R11: 10kΩ; RC0603FR-0710KL__R11
R12: 4.7kΩ; RC0603FR-074K7L__R12
R13: 4.7kΩ; RC0603FR-074K7L__R13
R14: 10kΩ; RC0603FR-0710KL__R14
R15: 10kΩ; RC0603FR-0710KL__R15
R16: 1kΩ; RC0603FR-071KL__R16
R17: 1MΩ; RC0603FR-071ML__R17
R18: 1MΩ; RC0603FR-071ML__R18
R19: 1MΩ; RC0603FR-071ML__R19
R20: 470kΩ; RC0603FR-07470KL__R20
R21: 10kΩ; RC0603FR-0710KL__R21
R22: 100kΩ; RC0603FR-07100KL__R22
R23: 100kΩ; RC0603FR-07100KL__R23
SW1: OS102011MS2QN1; OS102011MS2QN1__SW1
SW2: SW2; TS-1088-AR02016__SW2
U1: STM32F072CBT6; STM32F072CBT6__U1
U2: AS5600-ASOM; AS5600-ASOM__U2
U3: MB85RC256VPNF-G-AMERE2; MB85RC256VPNF-G-AMERE2__U3
U4: BQ24074RGTR; BQ24074RGTR__U4
U5: TLV75533PDBVR; TLV75533PDBVR__U5
U6: USBLC6-2SC6; USBLC6-2SC6__U6

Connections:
BAT: C4.1, J2.1, R17.1, U4.2, U4.3
BAT_ADC: C17.1, R17.2, R18.1, U1.17
BOOT0: J5.1, R10.1, U1.44
CC1: J1.6, R1.1
CC2: J1.12, R2.1
CHG_CE: R21.2, U1.20, U4.4
CHG_EN1: R6.1, U1.12, U4.6
CHG_EN2: R7.1, U1.13, U4.5
CHG_STAT: R9.2, U1.15, U4.9
COUNT_RESET: R15.1, SW2.1, U1.11
GND: C1.2, C2.2, C3.2, C4.2, C5.2, C6.2, C7.2, C8.2, C9.2, C10.2, C11.2, C12.2, C13.2, C14.2, C15.2, C16.2, C17.2, C18.2, C19.2, D1.1, J1.1, J1.2, J1.3, J1.4, J1.13, J1.14, J2.2, J3.2, J4.5, LED1.2, R1.2, R2.2, R3.2, R4.2, R5.2, R6.2, R7.2, R10.2, R18.2, R20.2, R23.2, SW1.1, SW2.2, U1.8, U1.23, U1.35, U1.47, U2.4, U2.8, U3.1, U3.2, U3.3, U3.4, U3.7, U4.8, U4.17, U5.2, U6.2
ILIM: R4.1, U4.12
ISET: R3.1, U4.16
LED: R16.1, U1.16
LED_A: LED1.1, R16.2
NRST: C13.1, J4.4, R11.1, U1.7
NTC: J3.1, R22.1, U4.1
PGOOD: R8.2, U1.14, U4.7
SCL: R13.2, U1.42, U2.7, U3.6
SCROLL_EN: R14.1, SW1.2, U1.10
SDA: R12.2, U1.43, U2.6, U3.5
SWCLK: J4.3, U1.37
SWDIO: J4.2, U1.34
SYS: C3.1, C5.1, U4.10, U4.11, U5.1, U5.3
TEMP_ADC: C19.1, R22.2, R23.1, U1.19
TMR: R5.1, U4.14
USB_DM: J1.7, J1.9, U1.32, U6.1, U6.6
USB_DP: J1.8, J1.10, U1.33, U6.3, U6.4
V3V3: C6.1, C7.1, C8.1, C9.1, C10.1, C11.1, C12.1, C14.1, C15.1, C16.1, J4.1, J5.2, R8.1, R9.1, R11.2, R12.1, R13.1, R14.2, R15.2, R21.1, U1.1, U1.9, U1.24, U1.36, U1.48, U2.1, U2.2, U3.8, U5.5
VBUS: C1.1, C2.1, D1.2, J1.15, J1.16, R19.1, U4.13, U6.5
VBUS_ADC: C18.1, R19.2, R20.1, U1.18

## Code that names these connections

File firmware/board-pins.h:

// SPDX-License-Identifier: MIT
// Generated by scripts/generate-board-pins.py; edit reference/rp2040.json.
#pragma once
#define PIN_MODE_BTN 0u
#define PIN_PERIPH_EN 1u
#define PIN_SDA 4u
#define PIN_SCL 5u
#define PIN_LCD_RST 16u
#define PIN_LCD_CS 17u
#define PIN_SPI_SCK 18u
#define PIN_SPI_MOSI 19u
#define PIN_ENC_A 20u
#define PIN_ENC_B 21u
#define PIN_LCD_DC 22u
#define PIN_LCD_BL 23u
#define BOARD_SYSTEM_CLOCK_HZ 48000000u
#define BOARD_I2C_HZ 300000u
#define BOARD_SPI_HZ 12000000u
#define BOARD_ENCODER_MAX_STEP_RATE 400000u
